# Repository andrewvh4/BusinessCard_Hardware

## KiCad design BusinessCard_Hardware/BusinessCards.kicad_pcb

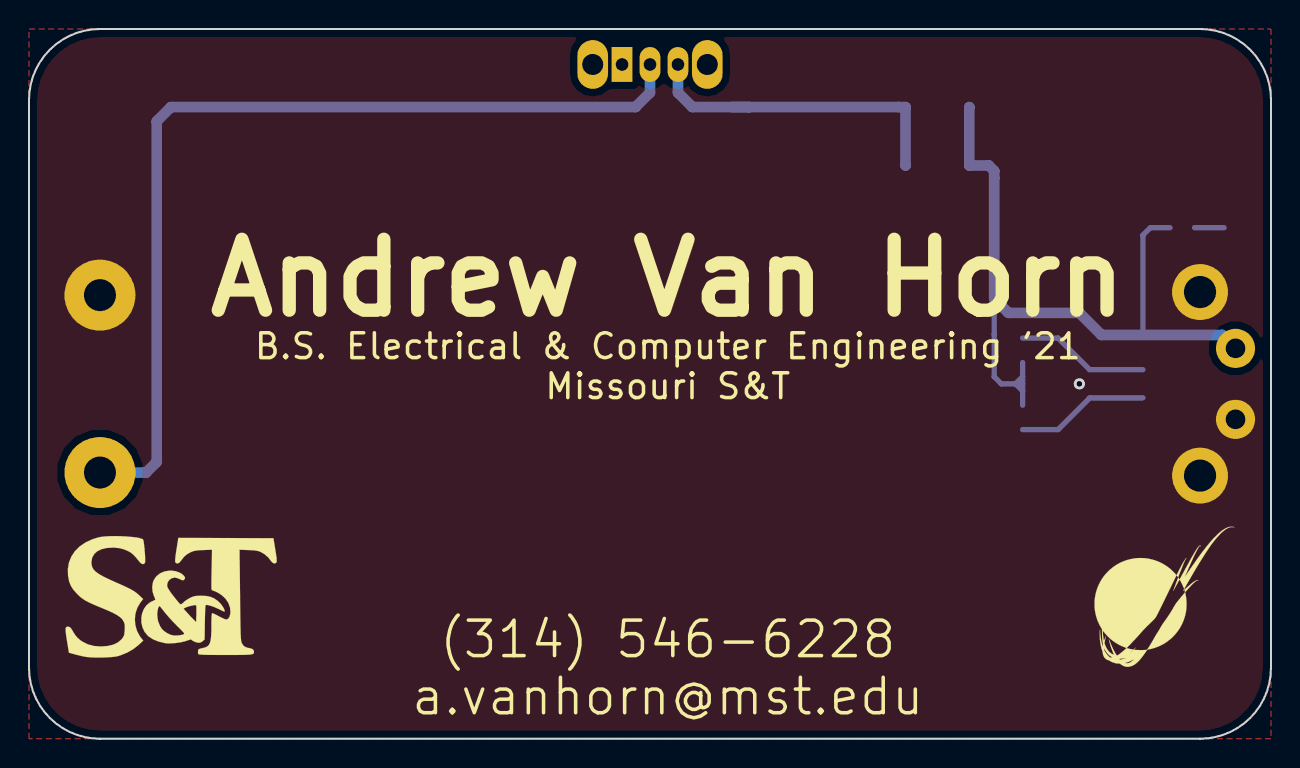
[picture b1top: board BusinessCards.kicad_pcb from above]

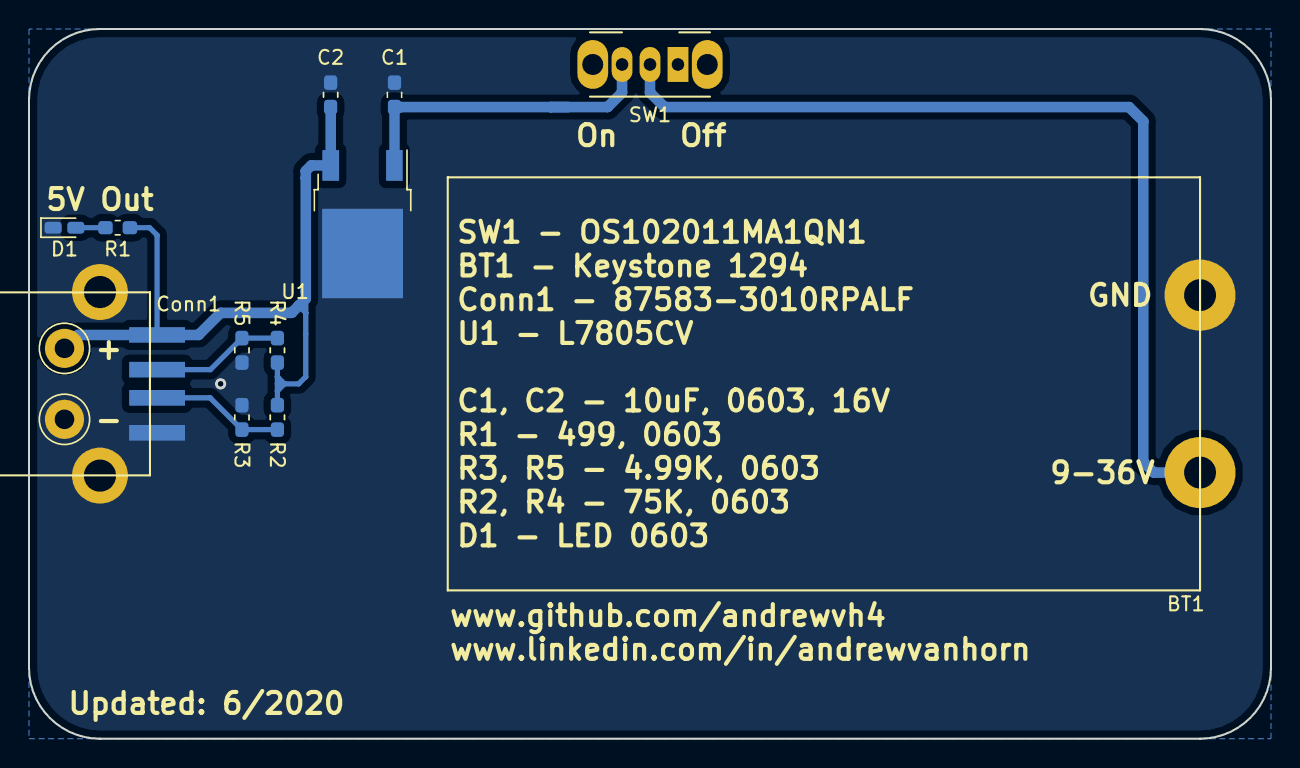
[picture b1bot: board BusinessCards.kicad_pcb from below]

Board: 2 copper layers, 88.9 x 50.8 mm, 12 parts (12 on the bottom side), 7 nets.

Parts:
BT1: Battery; 9V Battery Holder_36-1294-ND
C1, C2: 10uF; C_0603_1608Metric_Pad1.05x0.95mm_HandSolder
Conn1: USB_A; USB A Receptacle
D1: LED; LED_0603_1608Metric_Castellated
R1: R; R_0603_1608Metric_Pad1.05x0.95mm_HandSolder
R2, R4: 75K; R_0603_1608Metric_Pad1.05x0.95mm_HandSolder
R3, R5: 4.99K; R_0603_1608Metric_Pad1.05x0.95mm_HandSolder
SW1: SW_SPST; SW_CuK_OS102011MA1QN1_SPDT_Angled
U1: L7805; TO-252-2

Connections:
+5V: C2.1, Conn1.1, R1.1, R2.1, R4.1, U1.3
+9V: BT1.1, SW1.2
GND: BT1.2, C1.2, C2.2, Conn1.4, Conn1.5, D1.1, R3.2, R5.2, U1.2
unnamed: C1.1, SW1.3, U1.1
unnamed: Conn1.2, R4.2, R5.1
unnamed: Conn1.3, R2.2, R3.1
unnamed: D1.2, R1.2

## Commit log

2019-07-25 added 5V LDO circuit
2019-07-25 Added images
2019-07-27 created gerbs
2020-05-26 Created BOM
2020-06-11 fixed battery holder outline
2020-06-11 updated gerbs
